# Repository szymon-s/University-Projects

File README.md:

# University-Projects
Projects made during attending university lectures.

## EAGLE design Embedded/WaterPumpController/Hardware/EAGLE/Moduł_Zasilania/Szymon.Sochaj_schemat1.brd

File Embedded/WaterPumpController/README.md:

Projekt Systemy Mikroprocesorowe i Wbudowane
====================================

## Autor: Szymon Sochaj  
Kierunek: Informatyka  

## Temat: Układ sterujący pompą cyrkulacyjną w instalacji wodnej.
Układ pozwalający wybrać użytkownikowi jeden z trzech dostępnych trybów działania pompy:  
* tryb manualny  
* tryb temperaturowy  
* tryb czasowy  

Projekt oparty na płytce deweloperskiej Nucleo32 z mikrokontrolerem STM32 L432KC.  
Komunikacja pomiędzy układem a użytkownikiem odbywa się przy pomocy wyświetlacza  
LCD 4x20 i klawiatury membranowej. Do pomiaru temperatury użyto czujnika DS18B20.

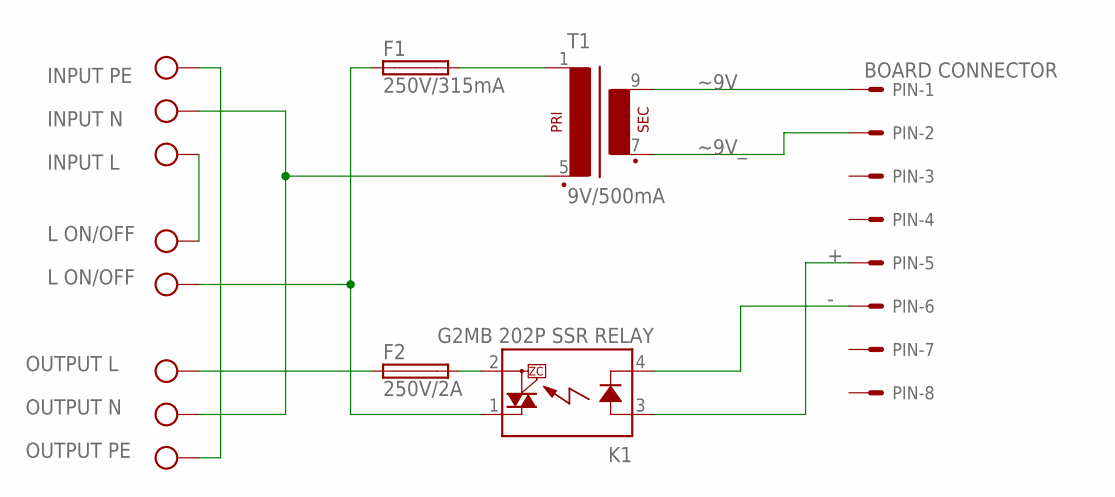
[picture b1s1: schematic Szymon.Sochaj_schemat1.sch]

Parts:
F1: 250V/315mA; SMIWPROJEKT_FUSE_HOLDER_5X20MM
F2: 250V/2A; SMIWPROJEKT_FUSE_HOLDER_5X20MM
K1: G2MB 202P SSR RELAY; SMIWPROJEKT_OMRON-G3MB-202P-SSR
PIN: BOARD CONNECTOR; CON-MOLEX_7395-08
T1: 9V/500mA; SMIWPROJEKT_VR11
X1, X2: CON-PTR500_AK300/3
X3: CON-PTR500_AK300/2

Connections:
+: K1.3 (A), PIN.5
-: K1.4 (K), PIN.6
L: F1.1, K1.1 (DS1), X3.2
L_IN: X1.1, X3.1
L_OUT: F2.1, X2.1
N: T1.5 (P2), X1.2, X2.2
unnamed: F2.2, K1.2 (DS2)
unnamed: F1.2, T1.1
PE: X1.3, X2.3
~9V: PIN.1, T1.9 (S4)
~9V_: PIN.2, T1.7 (S3)

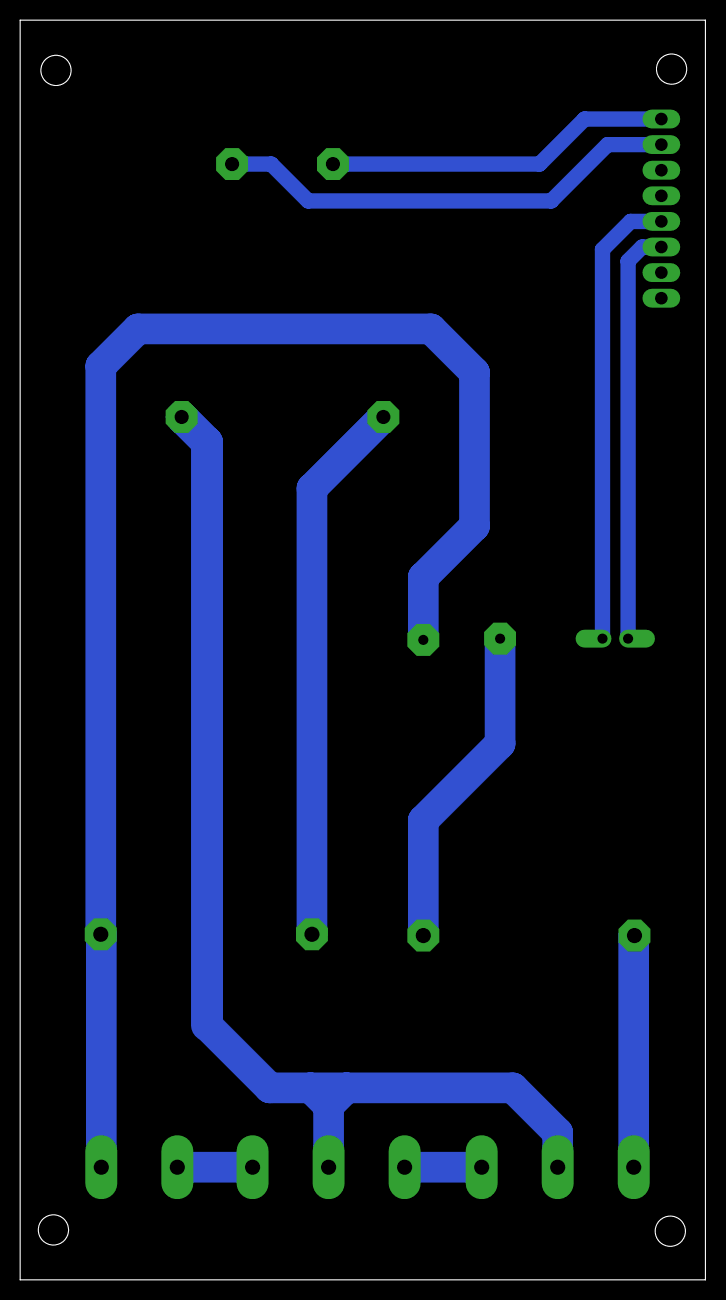
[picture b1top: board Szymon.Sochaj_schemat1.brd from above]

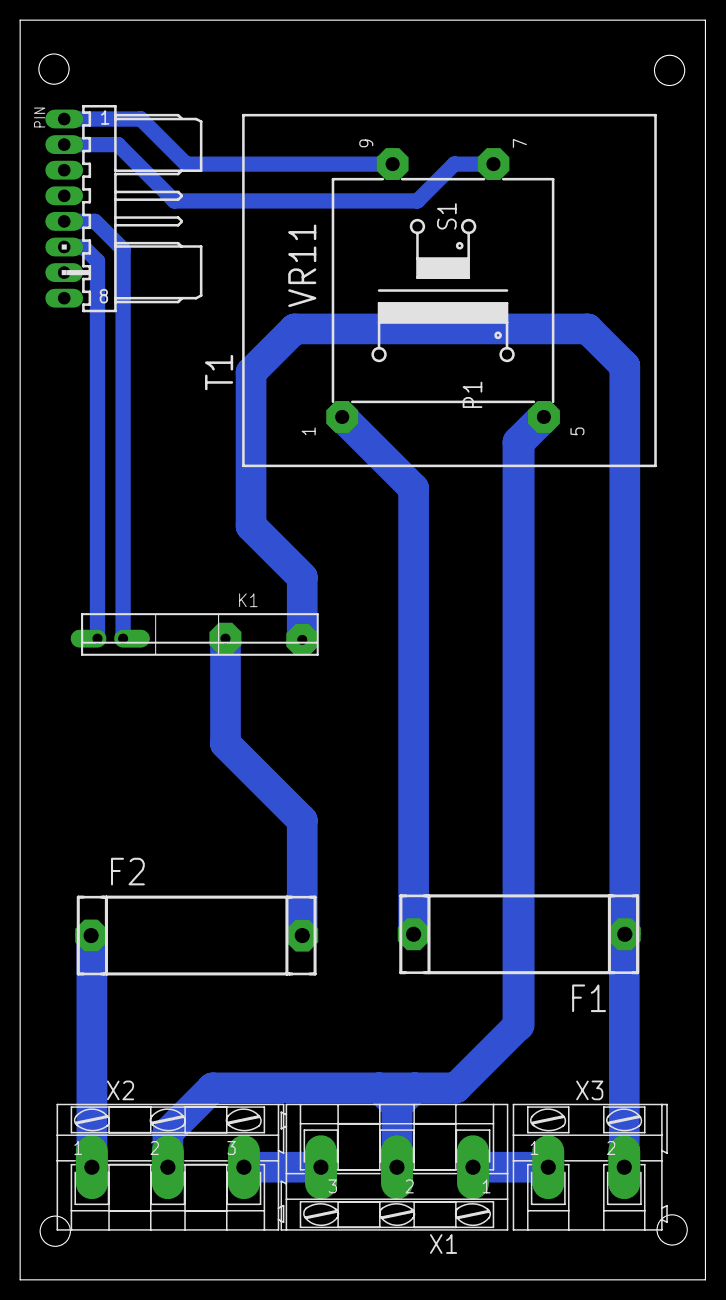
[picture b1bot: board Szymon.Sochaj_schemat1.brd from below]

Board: 2 copper layers, 68.0 x 125.0 mm, 8 parts (8 on the bottom side), 11 nets.

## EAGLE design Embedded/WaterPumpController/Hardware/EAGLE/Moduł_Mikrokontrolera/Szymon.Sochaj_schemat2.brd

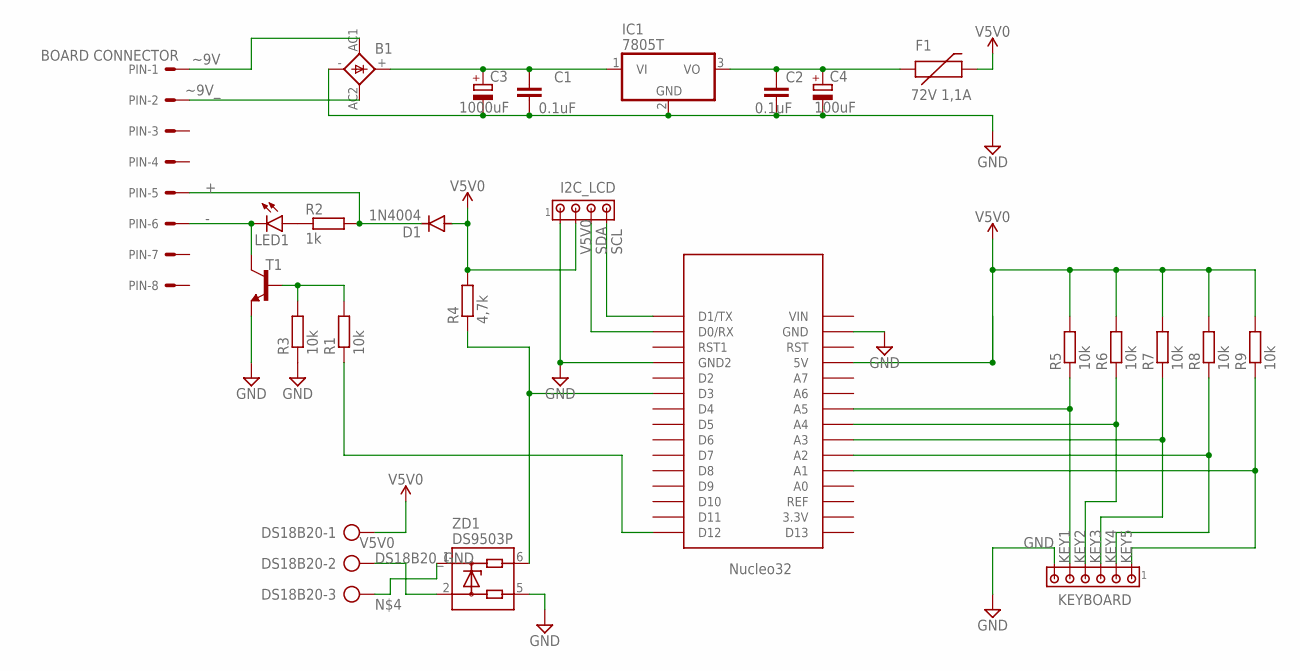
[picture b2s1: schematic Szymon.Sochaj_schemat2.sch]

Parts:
B1: 2KBP
C1, C2: 0.1uF; CAP-PTH-SMALL-KIT
C3: 1000uF; CAPPRD550W60D1200H2000B
C4: 100uF; CAPPRD550W60D1200H2000B
D1: 1N4004; DO41-10
DS18B20: AK300/3
F1: 72V 1,1A; PTC
I2C_LCD: MTA04-100; 10X04MTA
IC1: 7805T; TO220H
KEYBOARD: MTA06-100; 10X06MTA
LED1: LED3MM
PIN: BOARD CONNECTOR; 7395-08
R1, R3, R5, R6, R7, R8, R9: 10k; 0204/5
R2: 1k; 0204/5
R4: 4,7k; 0204/5
T1: BC337; TO92-ECB
U$1: NUCLEO32
ZD1: DS9503P; TSOC6

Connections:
+: D1.C, PIN.5, R2.2
-: LED1.K (C), PIN.6, T1.C (B)
DS18B20_GND: DS18B20.2, ZD1.2
GND: B1.-, C1.2, C2.2, C3.2 (-), C4.2 (-), I2C_LCD.1, IC1.2 (GND), KEYBOARD.6, R3.1, T1.E, U$1.GND, U$1.GND1 (GND2), ZD1.5
KEY1: KEYBOARD.5, R5.1, U$1.A5
KEY2: KEYBOARD.4, R6.1, U$1.A4
KEY3: KEYBOARD.3, R7.1, U$1.A3
KEY4: KEYBOARD.2, R8.1, U$1.A2
KEY5: KEYBOARD.1, R9.1, U$1.A1
unnamed: B1.+, C1.1, C3.1 (+), IC1.1 (VI)
unnamed: C2.1, C4.1 (+), F1.P$1 (1), IC1.3 (VO)
unnamed: DS18B20.3, ZD1.1
unnamed: LED1.A, R2.1
unnamed: R1.2, R3.2, T1.B (C)
unnamed: R1.1, U$1.D12
unnamed: R4.1, U$1.D3, ZD1.6
SCL: I2C_LCD.4, U$1.TX0 (D1/TX)
SDA: I2C_LCD.3, U$1.RX1 (D0/RX)
V5V0: D1.A, DS18B20.1, F1.P$2 (2), I2C_LCD.2, R4.2, R5.2, R6.2, R7.2, R8.2, R9.2, U$1.5V
~9V: B1.AC1, PIN.1
~9V_: B1.AC2, PIN.2

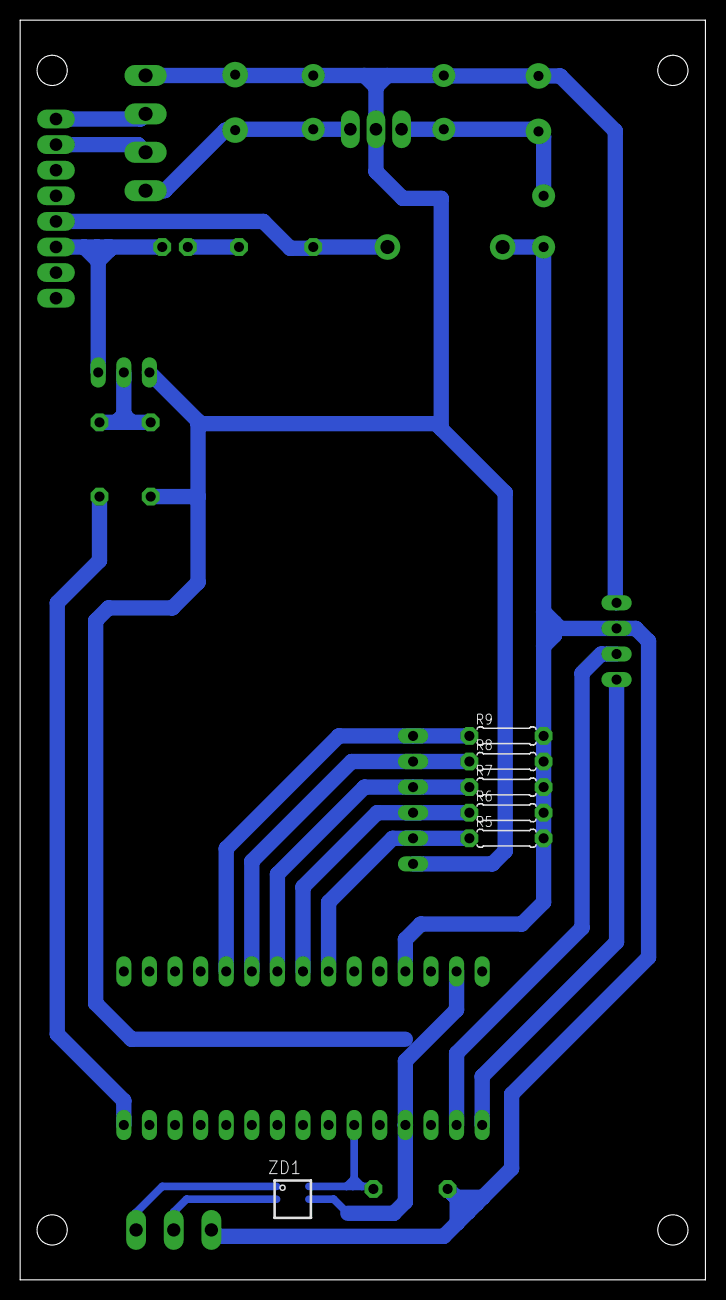
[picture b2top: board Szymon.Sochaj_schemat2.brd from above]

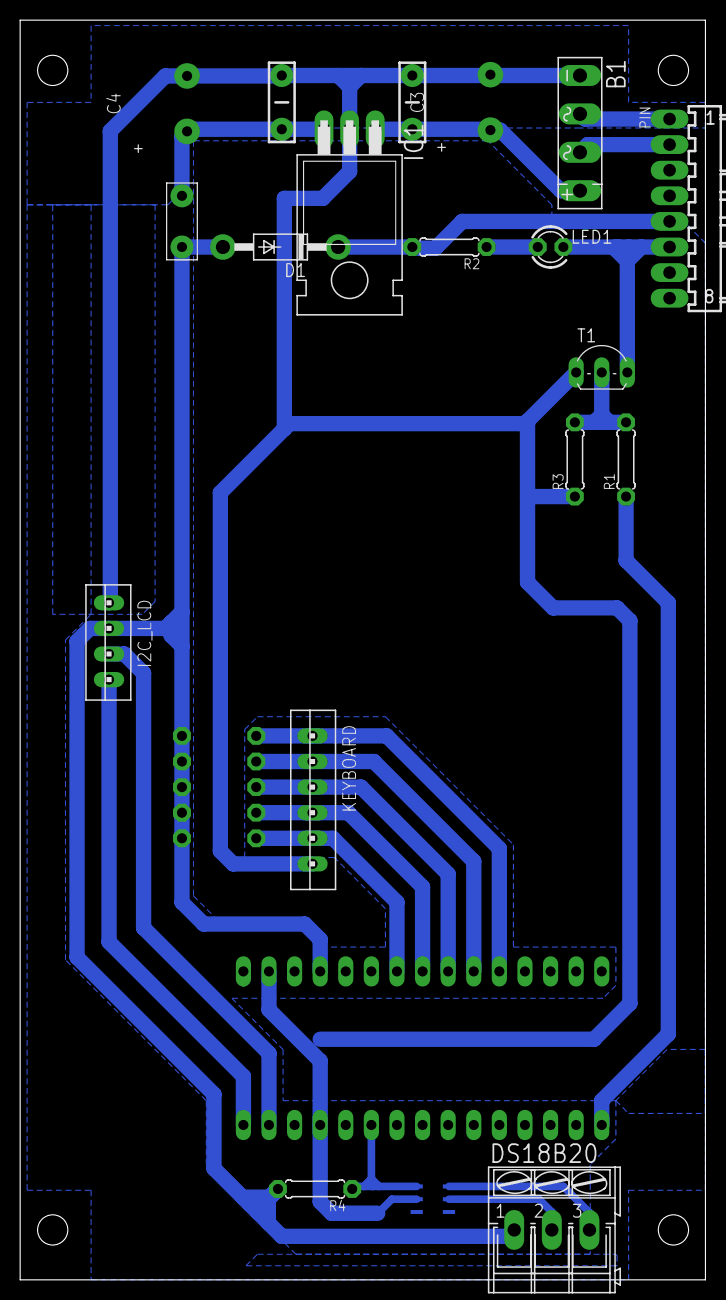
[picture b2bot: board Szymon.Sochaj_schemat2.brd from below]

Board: 2 copper layers, 68.0 x 125.0 mm, 25 parts (19 on the bottom side), 21 nets.

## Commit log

2021-05-05 SpaceAdventure
2021-05-05 Laplacian Filter for bitmap processing.
2021-05-05 Sort Visualization - Java Laboratory Classes
2021-05-05 Embedded project
2021-05-05 Android Kotlin app
